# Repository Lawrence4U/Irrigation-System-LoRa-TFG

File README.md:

# Irrigation-System-LoRa-TFG
Irrigation System designed around the LoRa communications protocol

#GUI.py
The python program contains a desktop applicatio to interact with the Arduino. YOu need to get your own api key to make the integration work

#LoRaSendAndReceive
Here the program for the Arduino is contained. As it is the case for the previous program, you should use our own keys for it to work.

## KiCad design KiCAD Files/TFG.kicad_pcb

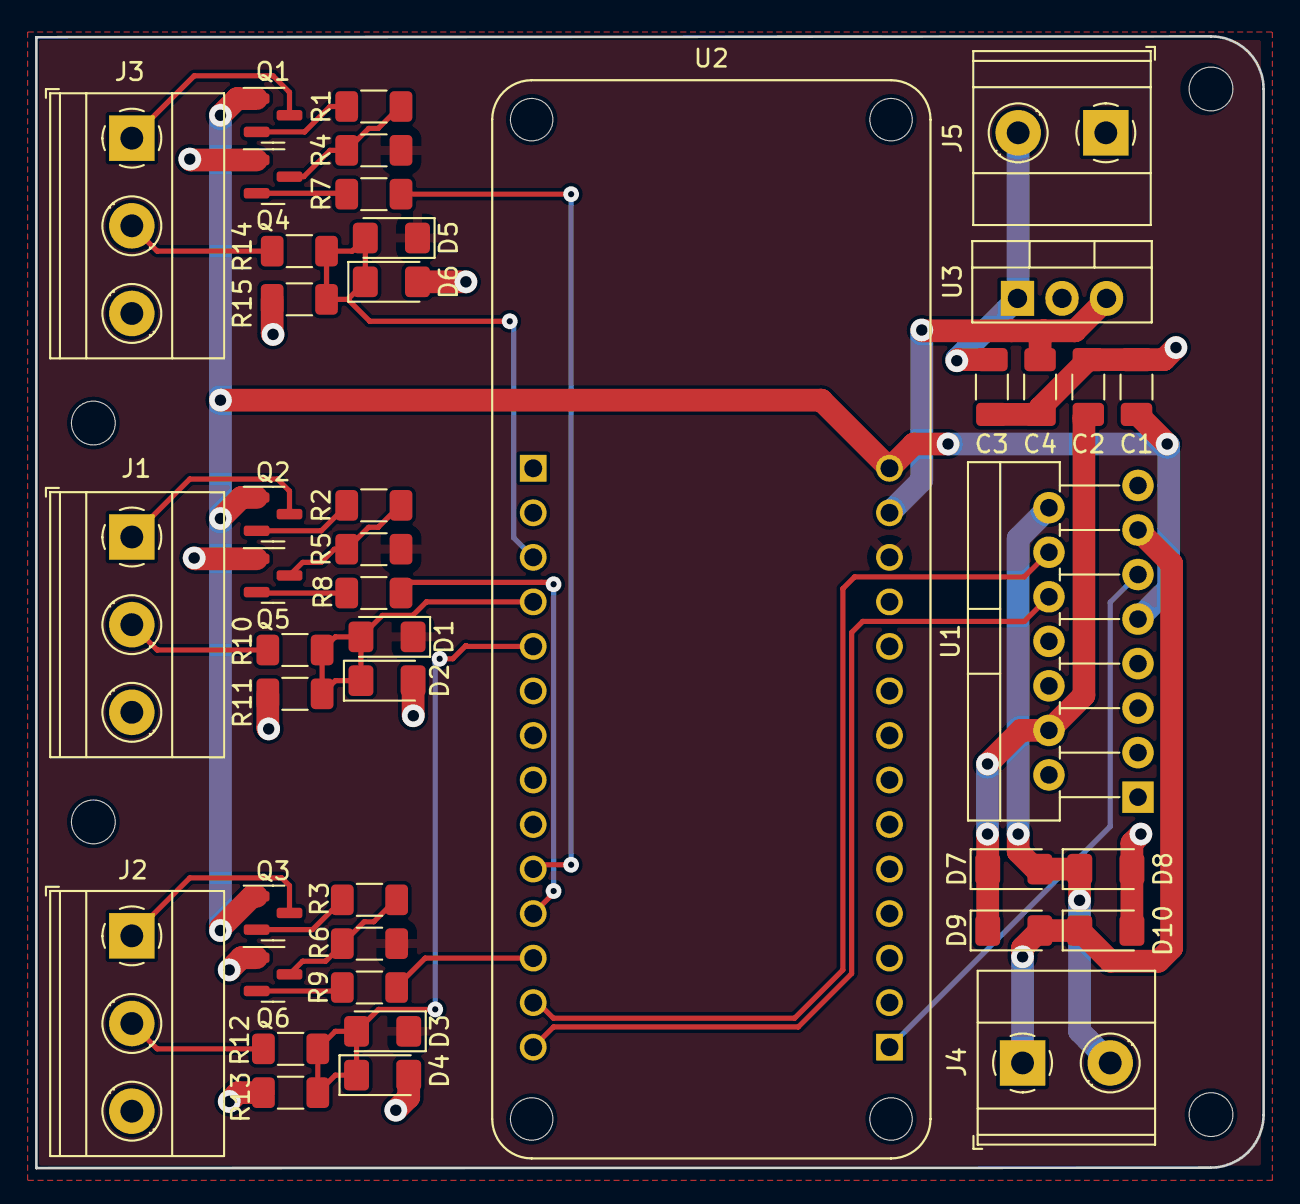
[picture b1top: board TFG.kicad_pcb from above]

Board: 2 copper layers, 70.0 x 64.5 mm, 46 parts (0 on the bottom side), 32 nets.

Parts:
C1, C2, C4: 0.1u; C_1206_3216Metric_Pad1.33x1.80mm_HandSolder
C3: 0.33u; C_1206_3216Metric_Pad1.33x1.80mm_HandSolder
D1, D2, D3, D4, D5, D6: 1N5711UR; D_1206_3216Metric_Pad1.42x1.75mm_HandSolder
D7, D8, D9, D10: 1N4007; D_1206_3216Metric_Pad1.42x1.75mm_HandSolder
J1, J2, J3: Screw_Terminal_01x03; TerminalBlock_Phoenix_MKDS-1,5-3_1x03_P5.00mm_Horizontal
J4, J5: Screw_Terminal_01x02; TerminalBlock_Phoenix_MKDS-1,5-2_1x02_P5.00mm_Horizontal
Q1, Q2, Q3: 2N3906; SOT-23
Q4, Q5, Q6: 2N3904; SOT-23
R1, R2, R3: 4.7k; R_1206_3216Metric_Pad1.30x1.75mm_HandSolder
R4, R5, R6: 10k; R_1206_3216Metric_Pad1.30x1.75mm_HandSolder
R7, R8, R9: 27k; R_1206_3216Metric_Pad1.30x1.75mm_HandSolder
R10, R12, R14: 1.7k; R_1206_3216Metric_Pad1.30x1.75mm_HandSolder
R11, R13, R15: 3.3k; R_1206_3216Metric_Pad1.30x1.75mm_HandSolder
REF324234, REF456456, REF2342344: MountingHole_2.5mm
U1: L298HN; TO-220-15_P2.54x2.54mm_StaggerOdd_Lead4.58mm_Vertical
U2: ARDUINO_MKR_ZERO; MODULE_ARDUINO_MKR_ZERO
U3: L7805; TO-220-3_Vertical

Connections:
+3V3: D1.1 (K), D3.1 (K), D5.1 (K), R4.2, R5.1, R6.1, U2.J5_12 (3V3)
+5V: C1.1, Q1.1 (E), Q2.1 (E), Q3.1 (E), U1.9 (Vss), U2.J5_14 (5V)
+12V: C2.1, D7.1 (K), D9.1 (K), U1.4 (Vs)
Earth: C1.2, C2.2, C3.2, C4.2, D2.2 (A), D4.2 (A), D6.2 (A), D8.2 (A), D10.2 (A), J1.3, J2.3, J3.3, J5.1, Q4.1 (E), Q5.1 (E), Q6.1 (E), R11.2, R13.2, R15.2, U1.8 (GND), U1.15 (SENSE_B), U2.J5_11 (GND), U3.2 (GND)
unnamed: C3.1, J5.2, U3.1 (IN)
unnamed: C4.1, U2.J5_13 (VIN), U3.3 (OUT)
unnamed: D1.2 (A), D2.1 (K), R10.2, R11.1, U2.J4_4 (A2)
unnamed: D3.2 (A), D4.1 (K), R12.2, R13.1, U2.J4_5 (A3)
unnamed: D5.2 (A), D6.1 (K), R14.2, R15.1, U2.J4_3 (A1)
unnamed: D7.2 (A), D8.1 (K), J4.2, U1.14 (OUT4)
unnamed: D9.2 (A), D10.1 (K), J4.1, U1.13 (OUT3)
unnamed: J1.1, Q2.3 (C)
unnamed: J1.2, R10.1
unnamed: J2.1, Q3.3 (C)
unnamed: J2.2, R12.1
unnamed: J3.1, Q1.3 (C)
unnamed: J3.2, R14.1
unnamed: Q1.2 (B), R1.2
unnamed: Q2.2 (B), R2.2
unnamed: Q3.2 (B), R3.2
unnamed: Q4.2 (B), R7.1
unnamed: Q4.3 (C), R1.1, R4.1
unnamed: Q5.2 (B), R8.1
unnamed: Q5.3 (C), R2.1, R5.2
unnamed: Q6.2 (B), R9.1
unnamed: Q6.3 (C), R3.1, R6.2
unnamed: R7.2, U2.J4_10 (1)
unnamed: R8.2, U2.J4_11 (2)
unnamed: R9.2, U2.J4_12 (3)
unnamed: U1.10 (IN3), U2.J4_14 (5)
unnamed: U1.11 (EnB), U2.J5_1 (6)
unnamed: U1.12 (IN4), U2.J4_13 (4)

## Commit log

2022-06-22 Project
2022-06-22 Privacy
2022-07-03 Added KiCad Schematics and PCB Design
2022-07-05 Añadidos los ficheros de configuración de GUI.py
2022-07-05 Added required files for app
2022-07-05 QOL improve
2022-07-05 Valve works properly now
2022-07-13 Añadidas las claves al secrets.h
2022-07-19 Añadida versión para 4 sensores de humedad
2022-09-13 Añadida última versión de GUI
2022-10-01 Rediseñando GUI
2022-10-01 idea WIP
2022-10-03 cambios ayer
2022-10-05 qwer
2022-10-15 cambios organizacion por place
2022-10-15 Añadido semanal
2022-10-15 Añadido primer start time y temrinado sabado
2022-10-16 Esqueleto completado
2022-10-16 Cambios de nombre de archivo
2022-10-18 Añadida opcion de añadir mas tiempos
2023-05-26 prettier sch
2023-05-26 chirpstack
2023-05-30 Config del GW introducida
2023-06-01 mqtt
2023-06-01 Añadido arduino para que fucnione
